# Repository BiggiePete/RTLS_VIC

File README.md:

# RTLS_VIC

Return to launch senior design kicad hardware repo for Vehicle In-flight Controller 

## Visit HTML BOM
https://biggiepete.github.io/RTLS_VIC/

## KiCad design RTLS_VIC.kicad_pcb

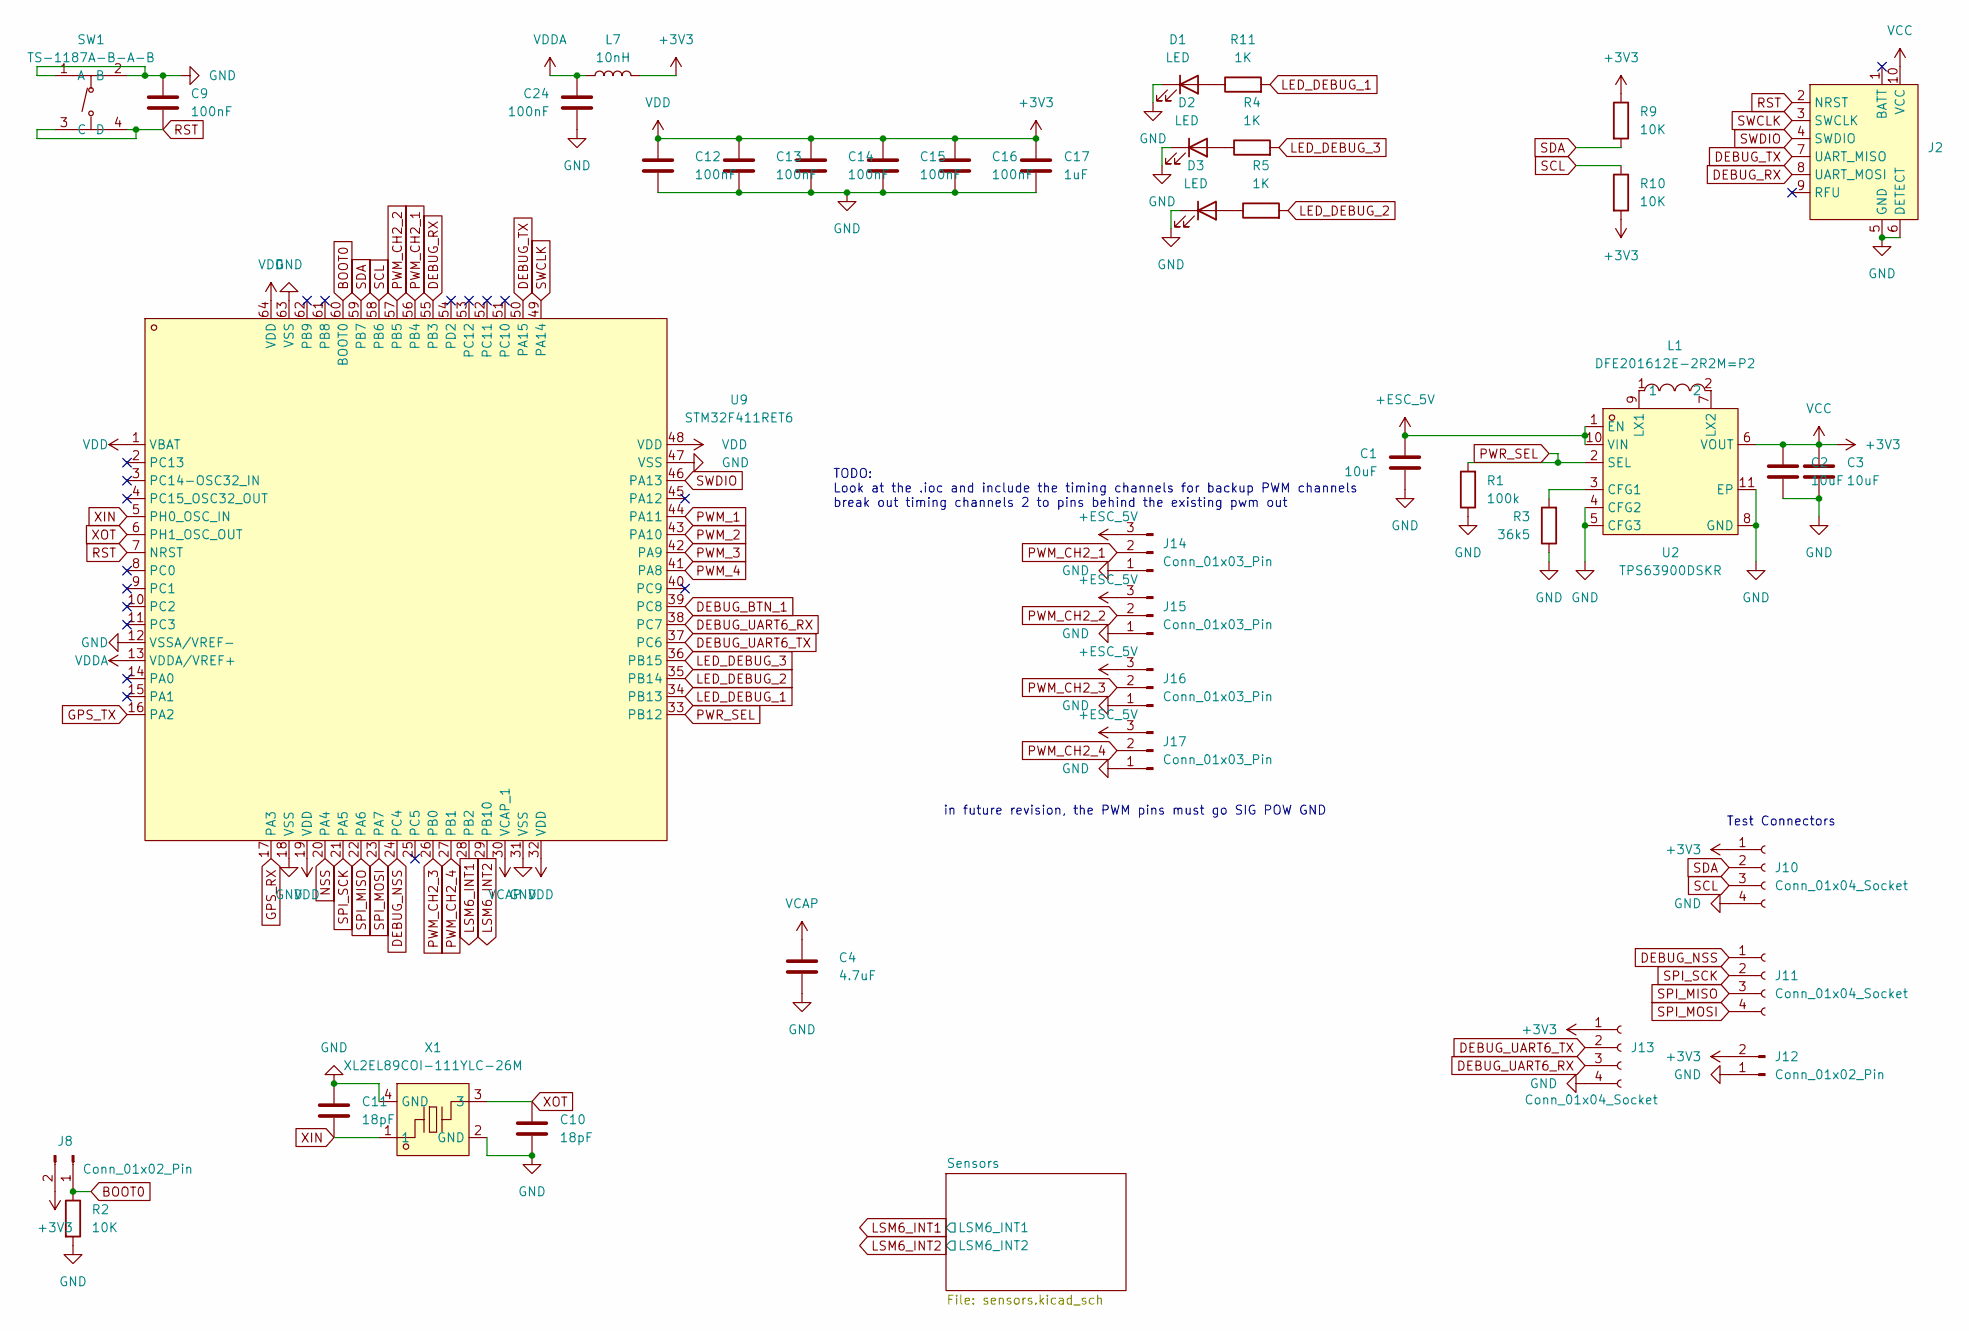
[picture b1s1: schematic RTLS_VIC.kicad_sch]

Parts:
C1, C2, C3: 10uF; C_0402_1005Metric; LCSC C15525
C4: 4.7uF; C_0402_1005Metric
C9, C12, C13, C14, C15, C16, C24: 100nF; C_0402_1005Metric
C10, C11: 18pF; C_0402_1005Metric
C17: 1uF; C_0402_1005Metric
D1, D2, D3: LED; LED_0603_1608Metric
J2: Tag-Connect_TC2050-IDC-NL_2x05_P1.27mm_Vertical
J8, J12: Conn_01x02_Pin; PinHeader_1x02_P2.54mm_Vertical
J10, J11, J13: Conn_01x04_Socket; PinSocket_1x04_P2.54mm_Vertical
J14, J15, J16, J17: Conn_01x03_Pin; PinHeader_1x03_P2.54mm_Vertical
L1: DFE201612E-2R2M=P2; L0806; LCSC Part C337893
L7: 10nH; L_0603_1608Metric; LCSC C913709
R1: 100k; R_0603_1608Metric; LCSC C25803
R2, R9, R10: 10K; R_0603_1608Metric
R3: 36k5; R_0603_1608Metric; LCSC C23029
R4, R5, R11: 1K; R_0603_1608Metric
SW1: TS-1187A-B-A-B; SW-SMD_4P-L5.1-W5.1-P3.70-LS6.5-TL_H1.5; LCSC Part C318884
U2: TPS63900DSKR; WSON-10_L2.5-W2.5-W0.50-TL-EP; LCSC Part C1518762
U9: STM32F411RET6; LQFP-64_L10.0-W10.0-P0.50-LS12.0-BL; LCSC Part C94355
X1: XL2EL89COI-111YLC-26M; CRYSTAL-SMD_4P-L3.2-W2.5-BL_SIT8008BI; LCSC Part C5444607

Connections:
+3V3: C2.1, C3.1, C12.1, C13.1, C14.1, C15.1, C16.1, C17.1, J2.10 (VCC), J8.2, J10.1, J12.2, J13.1, L7.2, R9.1, R10.2, U2.6 (VOUT), U9.1 (VBAT), U9.19 (VDD), U9.32 (VDD), U9.48 (VDD), U9.64 (VDD); also elsewhere on the board
+ESC_5V: C1.1, J14.3, J15.3, J16.3, J17.3, U2.1 (EN), U2.10 (VIN); also elsewhere on the board
BOOT0: J8.1, R2.1, U9.60 (BOOT0)
DEBUG_BTN_1: U9.39 (PC8); also elsewhere on the board
DEBUG_NSS: J11.1, U9.24 (PC4)
DEBUG_RX: J2.8 (UART_MOSI), U9.55 (PB3)
DEBUG_TX: J2.7 (UART_MISO), U9.50 (PA15)
DEBUG_UART6_RX: J13.3, U9.38 (PC7)
DEBUG_UART6_TX: J13.2, U9.37 (PC6)
GND: C1.2, C2.2, C3.2, C4.2, C9.1, C10.2, C11.1, C12.2, C13.2, C14.2, C15.2, C16.2, C17.2, C24.2, D1.1 (K), D2.1 (K), D3.1 (K), J2.5 (GND), J2.6 (DETECT), J10.4, J12.1, J13.4, J14.1, J15.1, J16.1, J17.1, R1.1, R2.2, R3.1, SW1.1 (A), SW1.2 (B), U2.4 (CFG2), U2.5 (CFG3), U2.8 (GND), U2.11 (EP), U9.12 (VSSA/VREF-), U9.18 (VSS), U9.31 (VSS), U9.47 (VSS), U9.63 (VSS), X1.2 (GND), X1.4 (GND); also elsewhere on the board
GPS_RX: U9.17 (PA3); also elsewhere on the board
GPS_TX: U9.16 (PA2); also elsewhere on the board
LED_DEBUG_1: R11.2, U9.34 (PB13)
LED_DEBUG_2: R5.2, U9.35 (PB14)
LED_DEBUG_3: R4.2, U9.36 (PB15)
LSM6_INT1: U9.28 (PB2); also elsewhere on the board
LSM6_INT2: U9.29 (PB10); also elsewhere on the board
NSS: U9.20 (PA4); also elsewhere on the board
unnamed: D1.2 (A), R11.1
unnamed: D2.2 (A), R4.1
unnamed: D3.2 (A), R5.1
unnamed: R3.2, U2.3 (CFG1)
unnamed: L1.1, U2.9 (LX1)
unnamed: L1.2, U2.7 (LX2)
PWM_1: U9.44 (PA11); also elsewhere on the board
PWM_2: U9.43 (PA10); also elsewhere on the board
PWM_3: U9.42 (PA9); also elsewhere on the board
PWM_4: U9.41 (PA8); also elsewhere on the board
PWM_CH2_1: J14.2, U9.56 (PB4)
PWM_CH2_2: J15.2, U9.57 (PB5)
PWM_CH2_3: J16.2, U9.26 (PB0)
PWM_CH2_4: J17.2, U9.27 (PB1)
PWR_SEL: R1.2, U2.2 (SEL), U9.33 (PB12)
RST: C9.2, J2.2 (NRST), SW1.3 (C), SW1.4 (D), U9.7 (NRST)
SCL: J10.3, R10.1, U9.58 (PB6); also elsewhere on the board
SDA: J10.2, R9.2, U9.59 (PB7); also elsewhere on the board
SPI_MISO: J11.3, U9.22 (PA6); also elsewhere on the board
SPI_MOSI: J11.4, U9.23 (PA7); also elsewhere on the board
SPI_SCK: J11.2, U9.21 (PA5); also elsewhere on the board
SWCLK: J2.3 (SWCLK), U9.49 (PA14)
SWDIO: J2.4 (SWDIO), U9.46 (PA13)
VCAP: C4.1, U9.30 (VCAP_1)
VDDA: C24.1, L7.1, U9.13 (VDDA/VREF+)
XIN: C11.2, U9.5 (PH0_OSC_IN), X1.1
XOT: C10.1, U9.6 (PH1_OSC_OUT), X1.3

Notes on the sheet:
TODO: Look at the .ioc and include the timing channels for backup PWM channels break out timing channels 2 to pins behind the existing pwm out
Test Connectors
in future revision, the PWM pins must go SIG POW GND

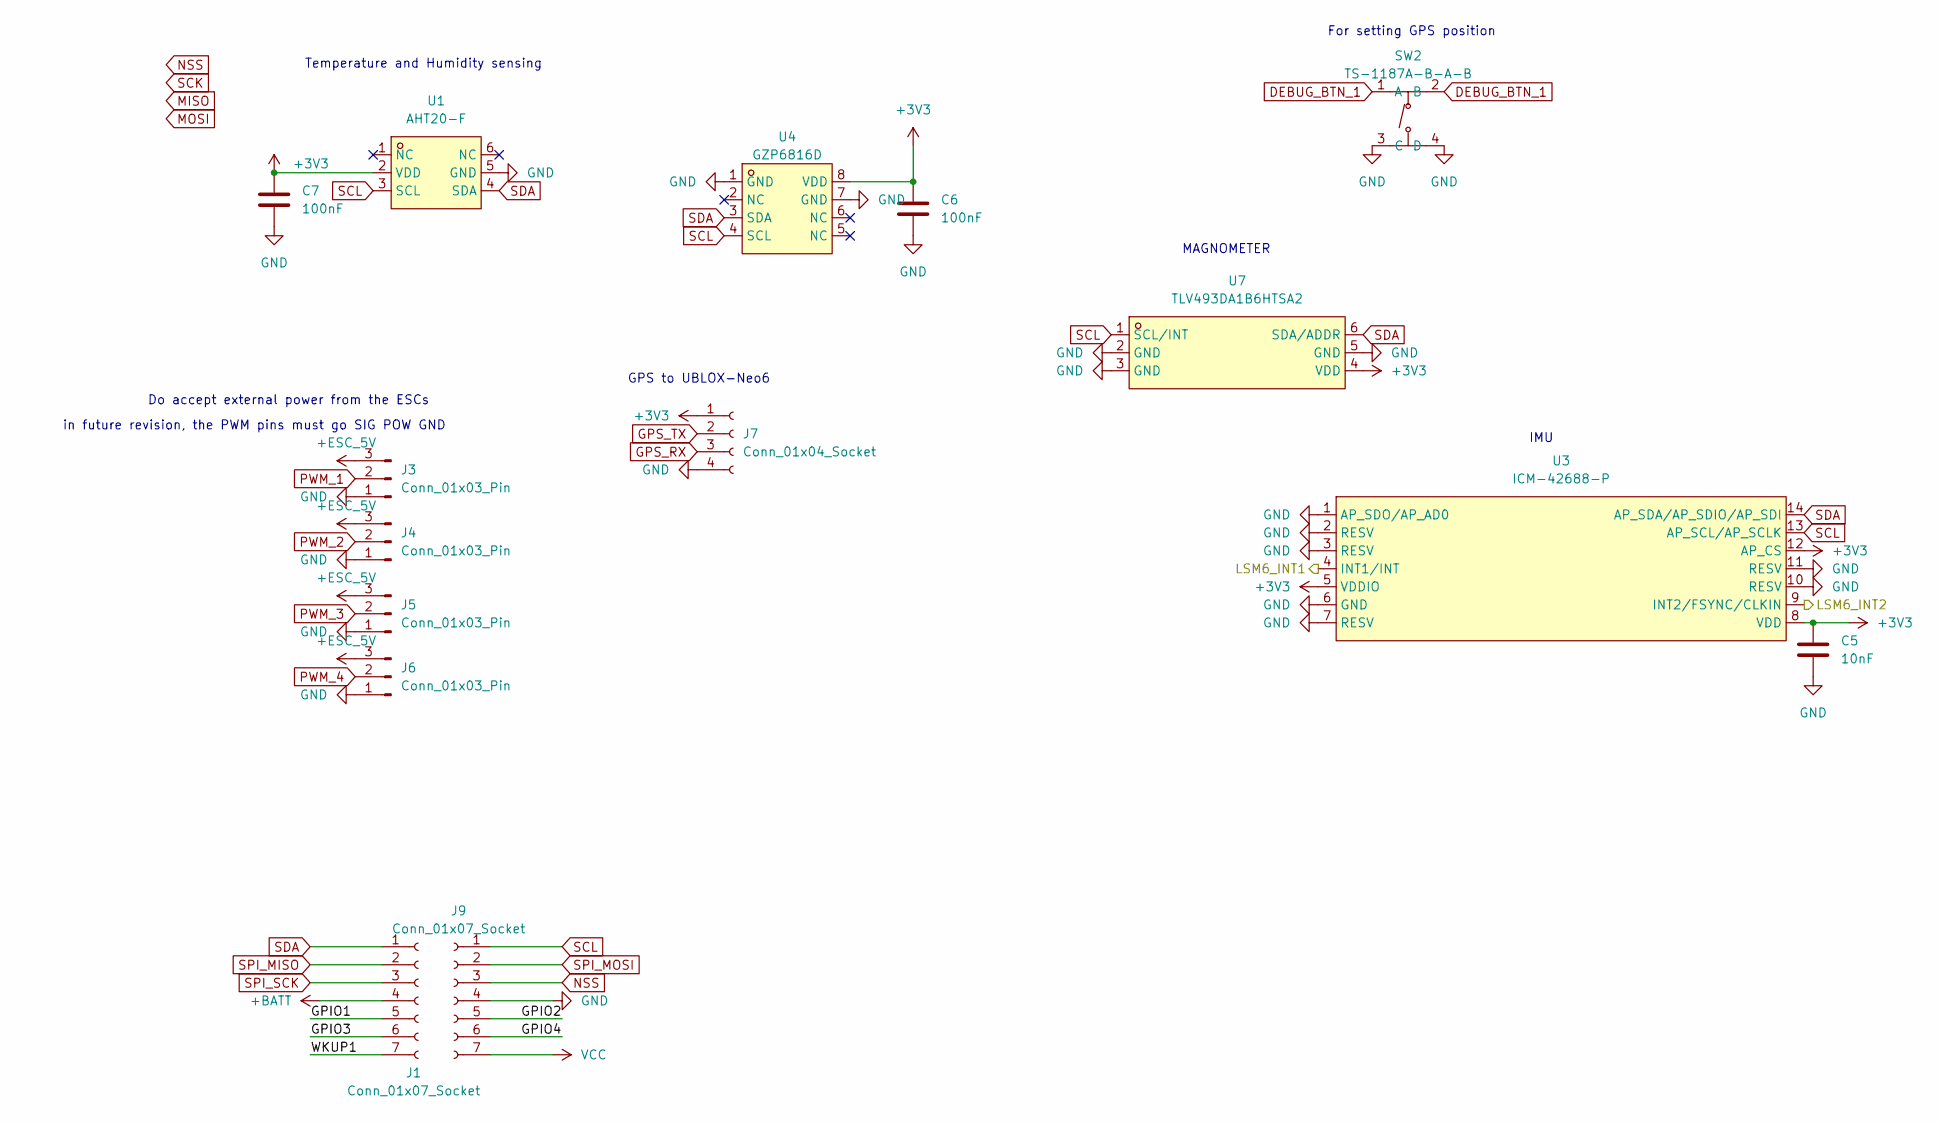
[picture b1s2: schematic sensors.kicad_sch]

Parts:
C5: 10nF; C_0402_1005Metric
C6, C7: 100nF; C_0402_1005Metric
J1, J9: Conn_01x07_Socket; PinHeader_1x07_P2.54mm_Vertical
J3, J4, J5, J6: Conn_01x03_Pin; PinHeader_1x03_P2.54mm_Vertical
J7: Conn_01x04_Socket; PinSocket_1x04_P2.54mm_Vertical
SW2: TS-1187A-B-A-B; SW-SMD_4P-L5.1-W5.1-P3.70-LS6.5-TL_H1.5; LCSC Part C318884
U1: AHT20-F; SENSOR-SMD-6_AHT20; LCSC Part C3012622
U3: ICM-42688-P; LGA-14_L3.0-W2.5-P0.50-TL; LCSC Part C1850418
U4: GZP6816D; SENSOR-SMD_XGZP6816D; LCSC Part C3038127
U7: TLV493DA1B6HTSA2; SOP-6_L3.0-W1.5-P0.95-LS2.5-BR; LCSC Part C126688

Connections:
+3V3: C5.1, C6.1, C7.1, J7.1, J9.7, U1.2 (VDD), U3.5 (VDDIO), U3.8 (VDD), U3.12 (AP_CS), U4.8 (VDD), U7.4 (VDD); also elsewhere on the board
+BATT: J1.4
+ESC_5V: J3.3, J4.3, J5.3, J6.3; also elsewhere on the board
/Sensors/GPIO1: J1.5
/Sensors/GPIO2: J9.5
/Sensors/GPIO3: J1.6
/Sensors/GPIO4: J9.6
/Sensors/WKUP1: J1.7
DEBUG_BTN_1: SW2.1 (A), SW2.2 (B); also elsewhere on the board
GND: C5.2, C6.2, C7.2, J3.1, J4.1, J5.1, J6.1, J7.4, J9.4, SW2.3 (C), SW2.4 (D), U1.5 (GND), U3.1 (AP_SDO/AP_AD0), U3.2 (RESV), U3.3 (RESV), U3.6 (GND), U3.7 (RESV), U3.10 (RESV), U3.11 (RESV), U4.1 (GND), U4.7 (GND), U7.2 (GND), U7.3 (GND), U7.5 (GND); also elsewhere on the board
GPS_RX: J7.3; also elsewhere on the board
GPS_TX: J7.2; also elsewhere on the board
LSM6_INT1: U3.4 (INT1/INT); also elsewhere on the board
LSM6_INT2: U3.9 (INT2/FSYNC/CLKIN); also elsewhere on the board
NSS: J9.3; also elsewhere on the board
PWM_1: J3.2; also elsewhere on the board
PWM_2: J4.2; also elsewhere on the board
PWM_3: J5.2; also elsewhere on the board
PWM_4: J6.2; also elsewhere on the board
SCL: J9.1, U1.3 (SCL), U3.13 (AP_SCL/AP_SCLK), U4.4 (SCL), U7.1 (SCL/INT); also elsewhere on the board
SDA: J1.1, U1.4 (SDA), U3.14 (AP_SDA/AP_SDIO/AP_SDI), U4.3 (SDA), U7.6 (SDA/ADDR); also elsewhere on the board
SPI_MISO: J1.2; also elsewhere on the board
SPI_MOSI: J9.2; also elsewhere on the board
SPI_SCK: J1.3; also elsewhere on the board

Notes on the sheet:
in future revision, the PWM pins must go SIG POW GND
MAGNOMETER
GPS to UBLOX-Neo6
IMU
Do accept external power from the ESCs
For setting GPS position
Temperature and Humidity sensing

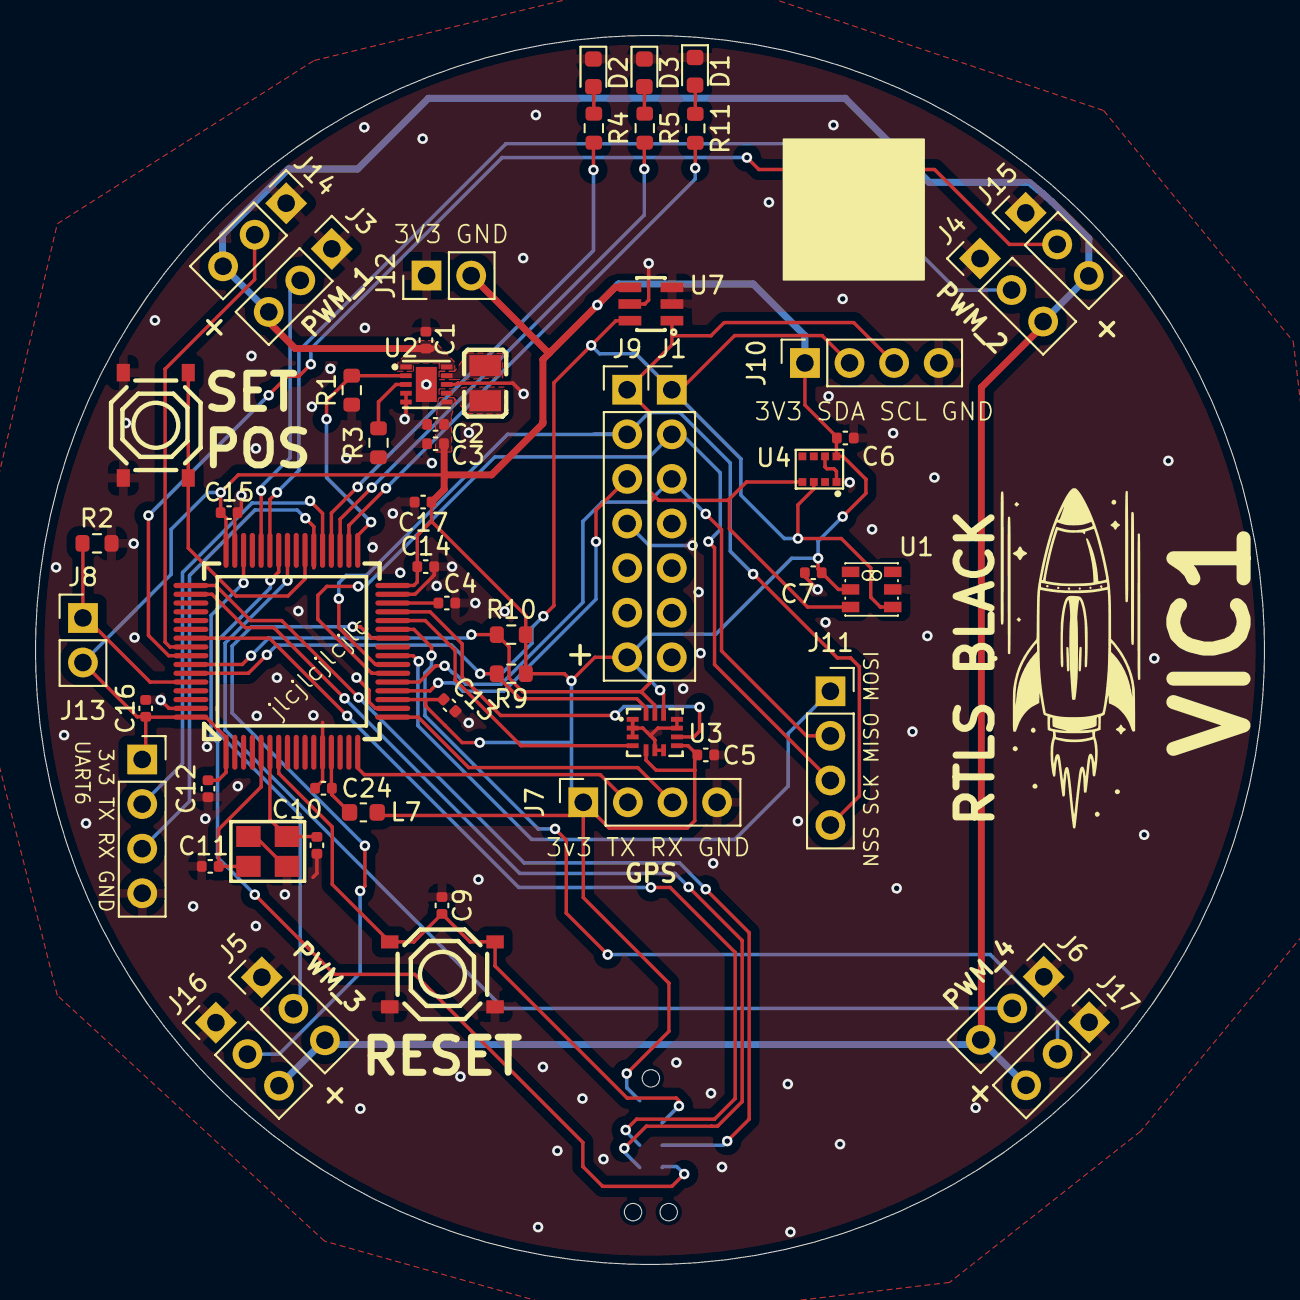
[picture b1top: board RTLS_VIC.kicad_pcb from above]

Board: 2 copper layers, 70.0 x 70.0 mm, 56 parts (1 on the bottom side), 45 nets.

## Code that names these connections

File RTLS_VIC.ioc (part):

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Mcu.Name=STM32F411R(C-E)Tx
Mcu.Package=LQFP64
Mcu.UserName=STM32F411RETx
PA10.Signal=S_TIM1_CH3
PA11.Signal=S_TIM1_CH4
PA13.Mode=Serial_Wire
PA13.Signal=SYS_JTMS-SWDIO
PA14.Mode=Serial_Wire
PA14.Signal=SYS_JTCK-SWCLK
PA15.Mode=Asynchronous
PA15.Signal=USART1_TX
PA2.Mode=Asynchronous
PA2.Signal=USART2_TX
PA3.Mode=Asynchronous
PA3.Signal=USART2_RX
PA5.Mode=Full_Duplex_Master
PA5.Signal=SPI1_SCK
PA6.Mode=Full_Duplex_Master
PA6.Signal=SPI1_MISO
PA7.Mode=Full_Duplex_Master
PA7.Signal=SPI1_MOSI
PA8.Signal=S_TIM1_CH1
PA9.Signal=S_TIM1_CH2
PB0.Signal=S_TIM3_CH3
PB1.Signal=S_TIM3_CH4
PB3.Mode=Asynchronous
PB3.Signal=USART1_RX
PB4.Signal=S_TIM3_CH1
PB5.Signal=S_TIM3_CH2
PB6.Mode=I2C
PB6.Signal=I2C1_SCL
PB7.Mode=I2C
PB7.Signal=I2C1_SDA
PC6.Mode=Asynchronous
PC6.Signal=USART6_TX
PC7.Mode=Asynchronous
PC7.Signal=USART6_RX
PH0\ -\ OSC_IN.Mode=HSE-External-Oscillator
PH0\ -\ OSC_IN.Signal=RCC_OSC_IN
PH1\ -\ OSC_OUT.Mode=HSE-External-Oscillator
PH1\ -\ OSC_OUT.Signal=RCC_OSC_OUT
RCC.HSE_VALUE=26000000
RCC.SYSCLKFreq_VALUE=100000000
RCC.SYSCLKSource=RCC_SYSCLKSOURCE_PLLCLK
board=custom

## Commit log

2025-04-18 getting somewhere
2025-04-26 add notes
2025-05-12 major overhaul
2025-05-13 html bom
2025-05-14 try new action
2025-05-14 list
2025-05-14 list bom dir
2025-05-14 rename command
2025-05-14 remake ibom.html
2025-05-14 working on placements
2025-05-15 nearly there
2025-05-16 preparing for prod
2025-05-16 build bom
2025-05-16 one more bom gen
2025-05-16 prod1
2025-05-16 forgot to do timing channel 2
2025-05-17 sponsor and timing
2025-05-17 fix resistor mis-sized
2025-05-19 fix issues with power supply
2025-05-19 add measurement
2025-05-21 initial boom arm cad and sim
2025-05-21 sim thrust math
2025-05-25 sync
2025-07-06 new cad models
2025-07-15 before first print
